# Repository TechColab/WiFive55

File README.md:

# WiFive55

https://hackaday.io/project/178964-wifive55

.. or see the PDF

### 2021-05-03
Moved opto-isolator slightly to move relay footprints enough to accomodate longer but cheap & popular Omron G3MB-202P.  
Moved Through-Hole-Technology version to new folder to differentiate from Surface-Mount-Technology version to follow.

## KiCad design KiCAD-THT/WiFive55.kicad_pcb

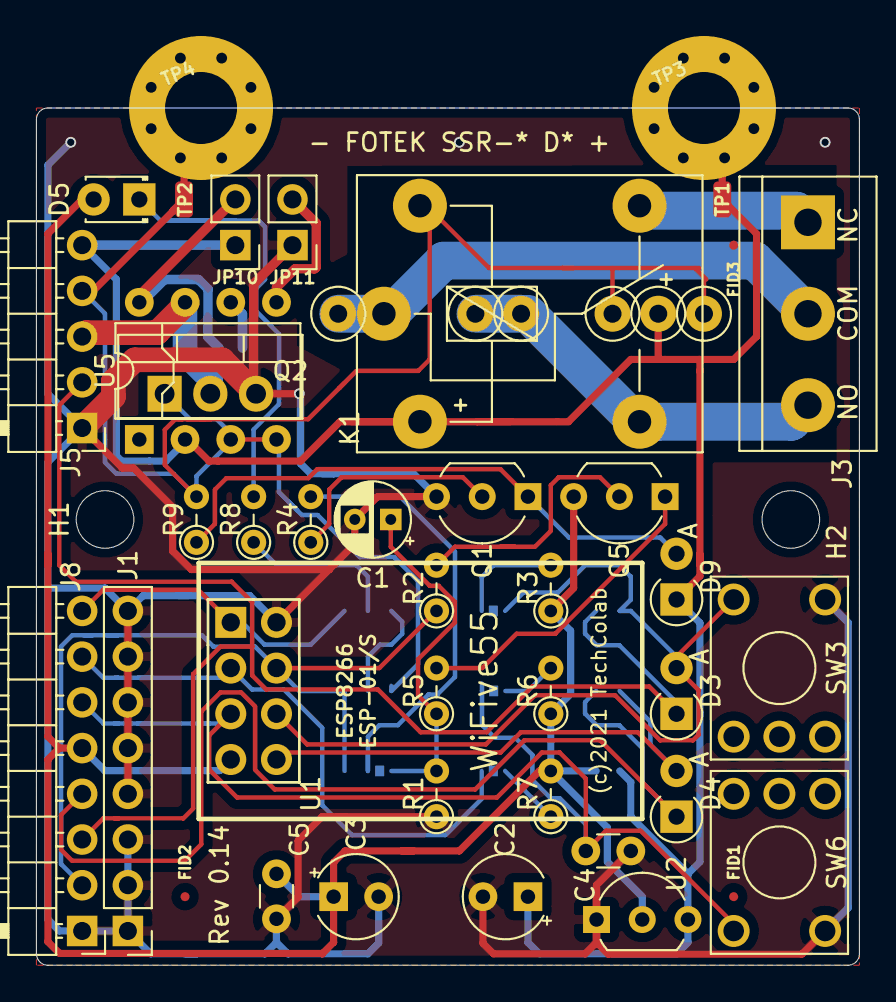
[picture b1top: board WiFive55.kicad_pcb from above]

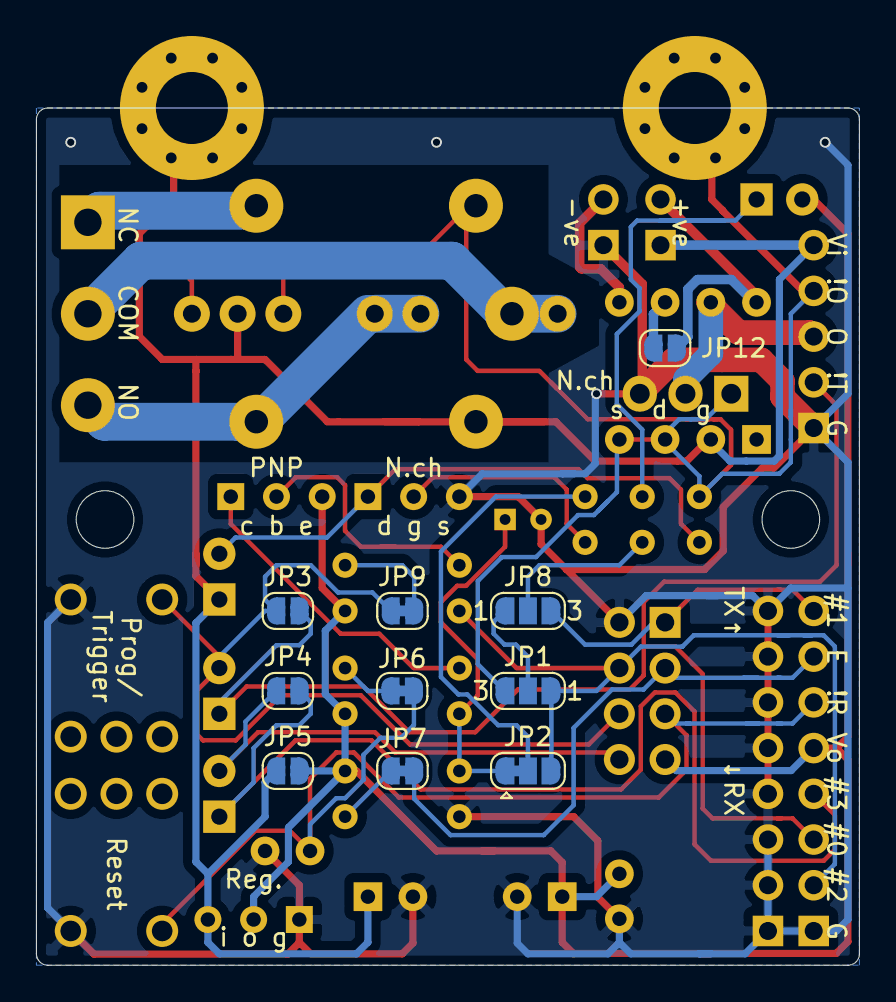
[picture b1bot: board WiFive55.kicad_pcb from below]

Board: 2 copper layers, 45.7 x 47.6 mm, 58 parts (10 on the bottom side), 31 nets.

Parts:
 : TestPoint_Loop_D1.80mm_Drill1.0mm_Beaded
 #2,  #3,  #4,  #5,  #6: TestPoint_Loop_D1.80mm_Drill1.0mm_Beaded
C1: 4.7; CP_Radial_D4.0mm_P2.00mm
C2, C3: 10; CP_Radial_Tantal_D4.5mm_P2.50mm
C4, C5: 0.1; C_Disc_D3.0mm_W1.6mm_P2.50mm
D3, D4: 1N5817 Schottky; D_A-405_P2.54mm_Vertical_AnodeUp
D5: LED; LED_D1.8mm_W3.3mm_H2.4mm
D9: 1N4148; D_A-405_P2.54mm_Vertical_AnodeUp
FID1, FID2, FID3: Fiducial; Fiducial_0.5mm_Mask1mm
H1, H2: MountingHole; MountingHole_3.2mm_M3
J1: Grounds; PinHeader_1x08_P2.54mm_Vertical
J3: Switched Output; TerminalBlock_bornier-3_P5.08mm
J5: 555-esque; PinHeader_1x05_P2.54mm_Horizontal
J8: Breadboard; PinHeader_1x08_P2.54mm_Horizontal
JP1: H/L; SolderJumper-3_P1.3mm_Open_RoundedPad1.0x1.5mm_NumberLabels
JP2: RC_bypass; SolderJumper-3_P1.3mm_Bridged12_RoundedPad1.0x1.5mm
JP3, JP4: Schottky bypass; SolderJumper-2_P1.3mm_Open_RoundedPad1.0x1.5mm
JP5: Reg?; SolderJumper-2_P1.3mm_Open_RoundedPad1.0x1.5mm
JP6: Rst; SolderJumper-2_P1.3mm_Bridged_RoundedPad1.0x1.5mm
JP7: Ena; SolderJumper-2_P1.3mm_Bridged_RoundedPad1.0x1.5mm
JP8: S/-; SolderJumper-3_P1.3mm_Open_RoundedPad1.0x1.5mm_NumberLabels
JP9: Prg; SolderJumper-2_P1.3mm_Bridged_RoundedPad1.0x1.5mm
JP10: Vin; PinHeader_1x02_P2.54mm_Vertical
JP11: GND; PinHeader_1x02_P2.54mm_Vertical
JP12: 6-pin; SolderJumper-2_P1.3mm_Open_RoundedPad1.0x1.5mm
K1: FINDER-36.11; Relay_SPDT_Finder_36.11
Q1: BS170; TO-92_Inline_Wide
Q2: IRF540N; TO-220-3_Vertical
Q5: BC557; TO-92_Inline_Wide
R1: 51k; R_Axial_DIN0204_L3.6mm_D1.6mm_P2.54mm_Vertical
R2, R3, R6, R7: 10k; R_Axial_DIN0204_L3.6mm_D1.6mm_P2.54mm_Vertical
R4: 200; R_Axial_DIN0204_L3.6mm_D1.6mm_P2.54mm_Vertical
R5: 8k2; R_Axial_DIN0204_L3.6mm_D1.6mm_P2.54mm_Vertical
R8: 470; R_Axial_DIN0204_L3.6mm_D1.6mm_P2.54mm_Vertical
R9: *; R_Axial_DIN0204_L3.6mm_D1.6mm_P2.54mm_Vertical
SW3: PRG; KSA_Tactile_SPST
SW6: RST; KSA_Tactile_SPST
TP1: VIN+; SolderWirePad_1x01_SMD_1x2mm
TP2: !OUT-; SolderWirePad_1x01_SMD_1x2mm
TP3: VIN+; MountingHole_4mm_Pad_Via
TP4: !OUT-; MountingHole_4mm_Pad_Via
U1: ESP-01/S; ESP-01
U2: 3.3Vdc 1A reg; TO-92L_Inline_Wide
U5: TLP250; DIP-8_W7.62mm

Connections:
+3V3: C3.1, C5.1, D5.2, J8.5, JP5.2, Q5.3, R3.1, R6.1, R7.2, U1.5, U2.2
+VDC: C2.1, D9.1, J5.5, JP5.1, JP10.1, K1.A1, TP1.1, TP3.1, U2.3, U5.2
/!OUT: J5.4, JP1.3, K1.A2, Q2.1, R9.2, TP2.1, TP4.1, U5.3, U5.4
/!RESET: C4.2, J8.6, JP6.2, SW6.2, U1.6
/!TRIGGER: D3.1, J5.2, J8.3, JP3.1
/COM: J3.2, K1.11
/ENABLE: J8.7, JP7.2, U1.7
/GPIO0: D3.2, JP3.2, JP9.2, SW3.1, U1.3
/GPIO1: J8.8, JP8.3, U1.8
/GPIO2: J8.2, JP1.1, JP2.3, R2.1, U1.2
/GPIO3: D4.2, JP4.2, U1.4
/NC: J3.1, K1.12
/NO: J3.3, K1.14
/OUT: J5.3, Q2.2, U5.7
/RX: D4.1, J8.4, JP4.1
GND: C1.2, C2.2, C3.2, C4.1, C5.2, J1.1, J1.2, J1.3, J1.4, J1.5, J1.6, J1.7, J1.8, J5.1, J8.1, JP11.1, Q1.3, Q2.3, R1.1, SW3.2, SW6.1, U1.1, U2.1
unnamed: C1.1, JP2.1, R1.2, R5.1
unnamed: D5.1, R8.2
unnamed: D9.2, Q1.1, R9.1
unnamed: JP1.2, JP8.1
unnamed: JP2.2, R4.2
unnamed: JP6.1, R6.2
unnamed: JP7.1, R7.1
unnamed: JP8.2, R8.1
unnamed: JP9.1, R3.2
unnamed: JP10.2, JP12.2, U5.8
unnamed: JP11.2, U5.5
unnamed: JP12.1, U5.6
unnamed: Q1.2, R4.1
unnamed: Q5.1, R5.2
unnamed: Q5.2, R2.2

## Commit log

2021-04-10 link to Hackaday
2021-04-15 update PCB for multiple SSR/RLA options
2021-04-15 alpha software screen-shots
2021-04-15 cropped PCB renders
2021-04-15 cropped PCB B-render
2021-04-15 cropped PCB B render again
2021-04-15 tidy temp files
2021-04-15 PCB v0.12
2021-04-24 Rev. 0.13 PCB
2021-05-03 Space for Omron G3MB-202P
2021-05-08 update silks

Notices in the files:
KiCAD-THT/WiFive55.kicad_pcb:
(c)2021 Phill Rogers @ TechColab.co.je
(c)2021 TechColab
